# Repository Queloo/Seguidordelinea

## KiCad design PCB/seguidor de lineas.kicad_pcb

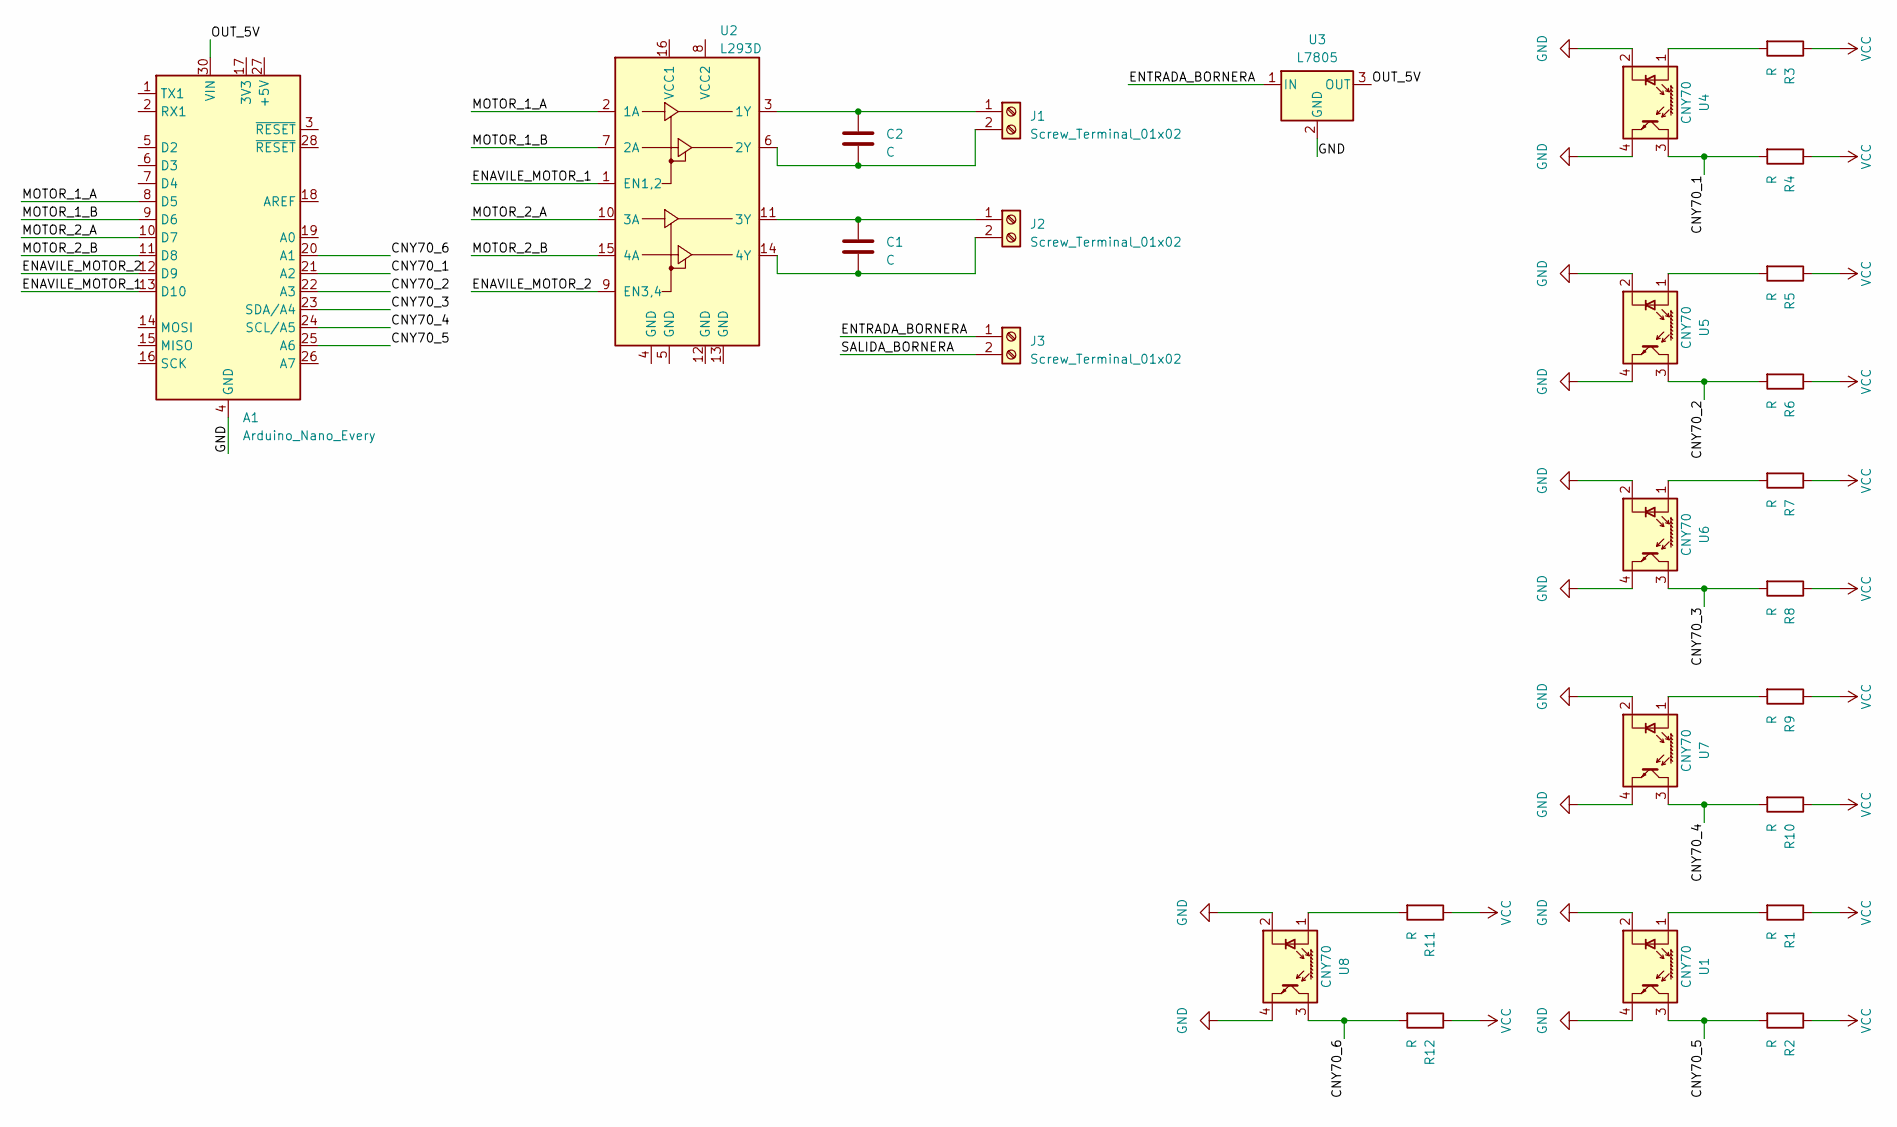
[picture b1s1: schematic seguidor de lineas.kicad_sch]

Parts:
A1: Arduino_Nano_Every; Arduino_Nano
C1, C2: C; CP_Radial_D5.0mm_P2.50mm
J1, J2, J3: Screw_Terminal_01x02; TerminalBlock_bornier-2_P5.08mm
R1, R2, R3, R4, R5, R6, R7, R8, R9, R10, R11, R12: R; R_Axial_DIN0204_L3.6mm_D1.6mm_P5.08mm_Horizontal
U1, U4, U5, U6, U7, U8: CNY70; Vishay_CNY70
U2: L293D; DIP-16_W7.62mm
U3: L7805; TO255P1020X450X2000-3

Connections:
/CNY70_1: A1.21 (A2), R4.2, U4.3 (C)
/CNY70_2: A1.22 (A3), R6.2, U5.3 (C)
/CNY70_3: A1.23 (SDA/A4), R8.2, U6.3 (C)
/CNY70_4: A1.24 (SCL/A5), R10.2, U7.3 (C)
/CNY70_5: A1.25 (A6), R2.2, U1.3 (C)
/CNY70_6: A1.20 (A1), R12.2, U8.3 (C); also elsewhere on the board
/ENAVILE_MOTOR_1: A1.13 (D10), U2.1 (EN1,2)
/ENAVILE_MOTOR_2: A1.12 (D9), U2.9 (EN3,4)
/ENTRADA_BORNERA: J3.1, U3.1 (IN)
/MOTOR_1_A: A1.8 (D5), U2.2 (1A)
/MOTOR_1_B: A1.9 (D6), U2.7 (2A)
/MOTOR_2_A: A1.10 (D7), U2.10 (3A)
/MOTOR_2_B: A1.11 (D8), U2.15 (4A)
/OUT_5V: A1.30 (VIN), U3.3 (OUT)
/SALIDA_BORNERA: J3.2
GND: A1.4 (GND), A1.29 (GND), U1.2 (K), U1.4 (E), U3.2 (GND), U4.2 (K), U4.4 (E), U5.2 (K), U5.4 (E), U6.2 (K), U6.4 (E), U7.2 (K), U7.4 (E), U8.2 (K), U8.4 (E); also elsewhere on the board
unnamed: C2.1, J1.1, U2.3 (1Y)
unnamed: C2.2, J1.2, U2.6 (2Y)
unnamed: C1.1, J2.1, U2.11 (3Y)
unnamed: C1.2, J2.2, U2.14 (4Y)
unnamed: R1.2, U1.1 (A)
unnamed: R3.2, U4.1 (A)
unnamed: R5.2, U5.1 (A)
unnamed: R7.2, U6.1 (A)
unnamed: R9.2, U7.1 (A)
unnamed 27: R11.2, U8.1 (A); also elsewhere on the board
VCC: R1.1, R2.1, R3.1, R4.1, R5.1, R6.1, R7.1, R8.1, R9.1, R10.1, R11.1, R12.1; also elsewhere on the board

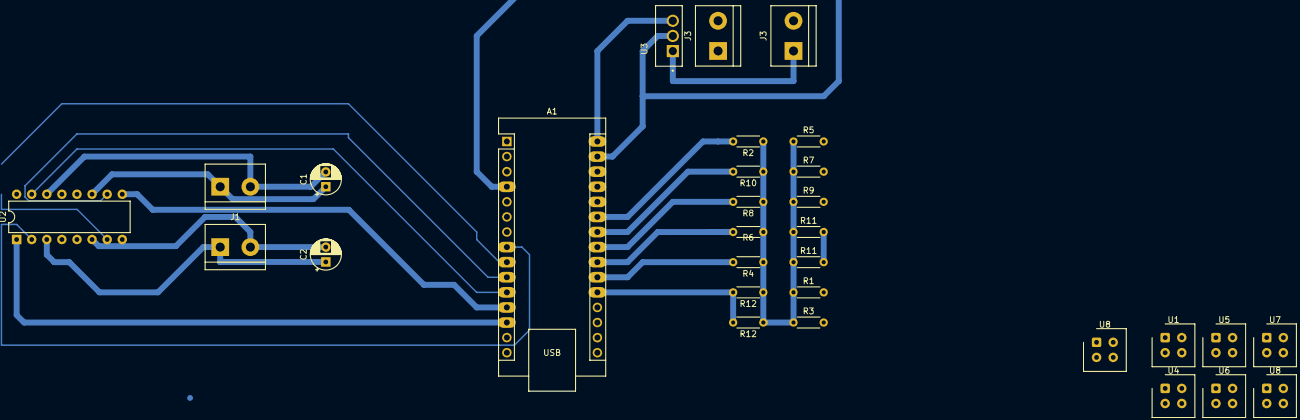
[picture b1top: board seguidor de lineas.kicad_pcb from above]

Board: 2 copper layers, 30 parts (0 on the bottom side), 26 nets.

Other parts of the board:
J3#2: Screw_Terminal_01x02; TerminalBlock_bornier-2_P5.08mm
R11#2, R12#2: R; R_Axial_DIN0204_L3.6mm_D1.6mm_P5.08mm_Horizontal
U8#2: CNY70; Vishay_CNY70

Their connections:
/CNY70_6: R12#2.2, U8#2.3 (C); also elsewhere on the board
GND: U8#2.2 (K), U8#2.4 (E); also elsewhere on the board
unnamed 27: R11#2.2, U8#2.1 (A); also elsewhere on the board
VCC: R11#2.1, R12#2.1; also elsewhere on the board

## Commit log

2024-04-17 prime carpt
